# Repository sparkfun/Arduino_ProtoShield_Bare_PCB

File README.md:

SparkFun Arduino ProtoShield - Bare PCB
=======================================

<table class="table table-hover table-striped table-bordered">
  <tr align="center">
   <td></td>
   <td></td>
  </tr>
  <tr align="center">
    <td>SparkFun Arduino ProtoShield - Bare PCB [ <a href="https://www.sparkfun.com/products/13819">DEV-13819</a> ]</td>
    <td>SparkFun ProtoShield Kit [ <a href="https://www.sparkfun.com/products/13820">DEV-13820</a> ]</td>
  </tr>
</table>

The SparkFun Arduino ProtoShield is a bare PCB with no attached or included parts that lets you customize your own Arduino shield using whatever circuit you can come up with! You will even be able to test your circuit or project to make sure everything is working the way it should! The SparkFun Arduino ProtoShield is based off the Arduino R3’s footprint that allows you to easily incorporate it with favorite Arduino-based device.

Repository Contents
-------------------
* **/Firmware** - Example code used in the hookup guide.
* **/Hardware** - All Eagle design files (.brd, .sch)
* **/Production** - All Eagle design files (.brd, .sch)

Documentation
--------------
* **[Hookup Guide](https://learn.sparkfun.com/tutorials/sparkfun-arduino-protoshield-hookup-guide)** - Basic hookup guide for the SparkFun Arduino ProtoShield v40.
* _**[Quickstart Guide (RETIRED)](https://learn.sparkfun.com/tutorials/arduino-protoshield-quickstart-guide)** - Basic quickstart guide for the SparkFun Arduino ProtoShield v25._

Product Versions
----------------
* [DEV-13819](https://www.sparkfun.com/products/13819) - Bare pcb.
* [DEV-13820](https://www.sparkfun.com/products/13820) - Protoshield Kit. Bare pcb, plus stackable headers, indicator LEDs, push buttons, and resistors.
* _[DEV-11665 (RETIRED)](https://www.sparkfun.com/products/11665) - Bare pcb._
* _[DEV-07914 (RETIRED)](https://www.sparkfun.com/products/7914) - Protoshield Kit. Bare pcb plus stackable headers, indicator LEDs, push buttons and resistors._

Version History
---------------
* [V_4.0F2.0](https://github.com/sparkfun/Arduino_ProtoShield_Bare_PCB/releases/tag/V_4.0F2.0) - Revision v4.0 with updated example code.
* [V_2.5F1.0](https://github.com/sparkfun/Arduino_ProtoShield_Bare_PCB/releases/tag/V_2.5F1.0) - Initial release with example code from quickstart guide 
* [V_2.5](https://github.com/sparkfun/Arduino_ProtoShield_Bare_PCB/releases/tag/V_2.5) - Initial release

License Information
-------------------

This product is _**open source**_! 

Please review the LICENSE.md file for license information. 

If you have any questions or concerns on licensing, please contact techsupport@sparkfun.com.

Distributed as-is; no warranty is given.

- Your friends at SparkFun.

_<COLLABORATION CREDIT>_

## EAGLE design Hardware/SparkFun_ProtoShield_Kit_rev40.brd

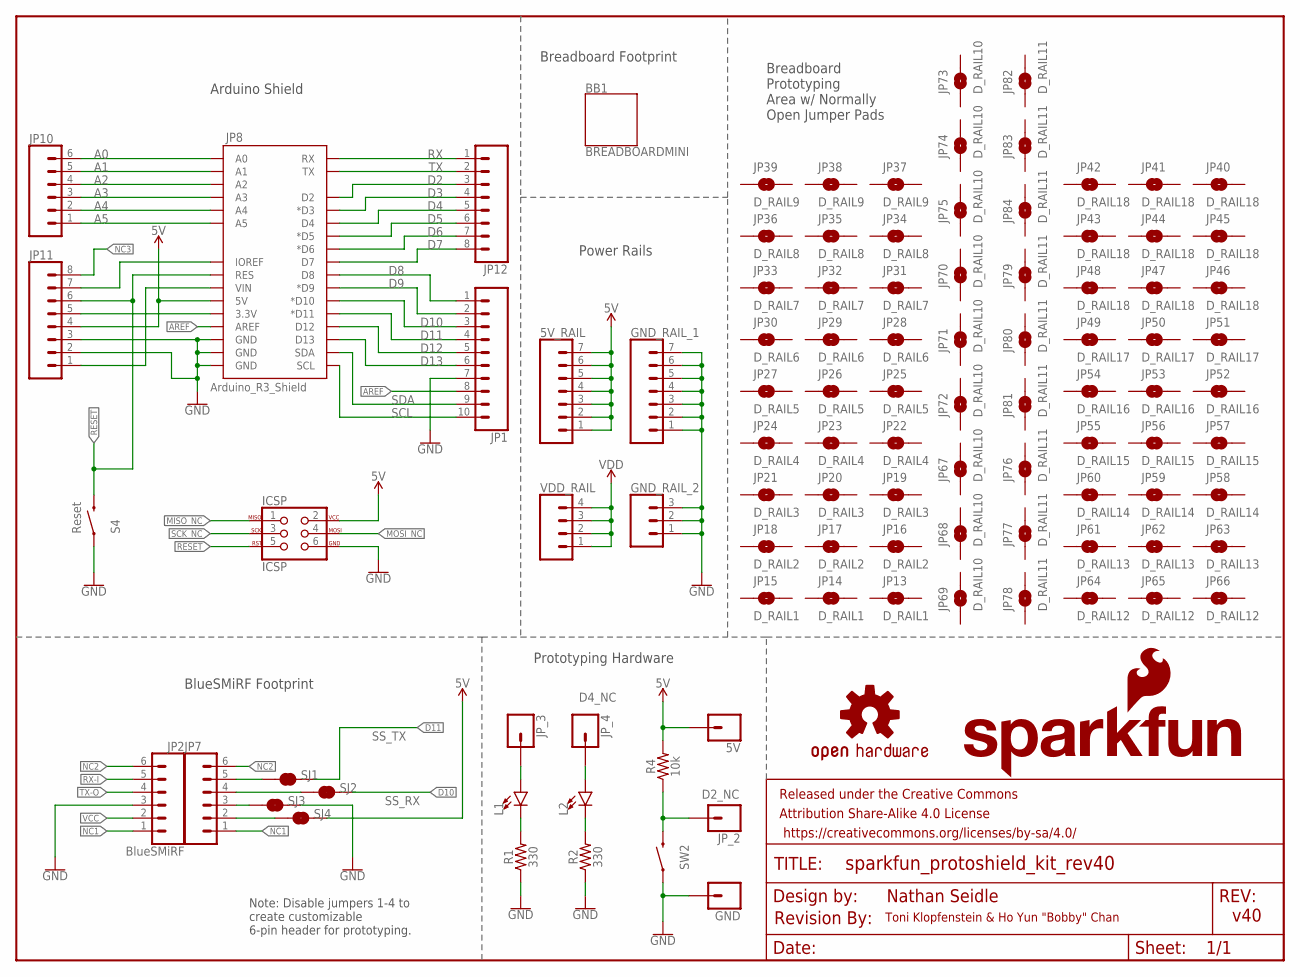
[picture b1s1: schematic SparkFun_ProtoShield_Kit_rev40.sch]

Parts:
5V: CONN_01; 1X01
5V_RAIL: CONN_07NO_SILK; 1X07_NO_SILK
BB1: BREADBOARDMINI; BREADBOARD-MINI
FRAME1: FRAME-LETTER; CREATIVE_COMMONS
GND: CONN_01; 1X01
GND_RAIL_1: CONN_07NO_SILK; 1X07_NO_SILK
GND_RAIL_2: CONN_031X03_NO_SILK; 1X03_NO_SILK
ICSP: ICSP; 2X3
JP1: CONN_10"; 1X10
JP2: BlueSMiRF; 1X06
JP7, JP10: CONN_06SILK_FEMALE_PTH; 1X06
JP8: ARDUINO_R3_SHIELDR3_PROTO_SHIELD; UNO_R3_PROTO_SHIELD
JP11, JP12: CONN_08"; 1X08
JP13, JP14, JP15: D_RAIL1; SMT-JUMPER_2_NO_NO-SILK
JP16, JP17, JP18: D_RAIL2; SMT-JUMPER_2_NO_NO-SILK
JP19, JP20, JP21: D_RAIL3; SMT-JUMPER_2_NO_NO-SILK
JP22, JP23, JP24: D_RAIL4; SMT-JUMPER_2_NO_NO-SILK
JP25, JP26, JP27: D_RAIL5; SMT-JUMPER_2_NO_NO-SILK
JP28, JP29, JP30: D_RAIL6; SMT-JUMPER_2_NO_NO-SILK
JP31, JP32, JP33: D_RAIL7; SMT-JUMPER_2_NO_NO-SILK
JP34, JP35, JP36: D_RAIL8; SMT-JUMPER_2_NO_NO-SILK
JP37, JP38, JP39: D_RAIL9; SMT-JUMPER_2_NO_NO-SILK
JP40, JP41, JP42, JP43, JP44, JP45, JP46, JP47, JP48: D_RAIL18; SMT-JUMPER_2_NO_NO-SILK
JP49, JP50, JP51: D_RAIL17; SMT-JUMPER_2_NO_NO-SILK
JP52, JP53, JP54: D_RAIL16; SMT-JUMPER_2_NO_NO-SILK
JP55, JP56, JP57: D_RAIL15; SMT-JUMPER_2_NO_NO-SILK
JP58, JP59, JP60: D_RAIL14; SMT-JUMPER_2_NO_NO-SILK
JP61, JP62, JP63: D_RAIL13; SMT-JUMPER_2_NO_NO-SILK
JP64, JP65, JP66: D_RAIL12; SMT-JUMPER_2_NO_NO-SILK
JP67, JP68, JP69, JP70, JP71, JP72, JP73, JP74, JP75: D_RAIL10; SMT-JUMPER_2_NO_NO-SILK
JP76, JP77, JP78, JP79, JP80, JP81, JP82, JP83, JP84: D_RAIL11; SMT-JUMPER_2_NO_NO-SILK
JP_2, JP_3, JP_4: CONN_01; 1X01
L1, L2: LED3MM; LED_3MM
LOGO1: OSHW-LOGOS; OSHW-LOGO-S
R1, R2: 330; AXIAL-0.3
R4: 10k; AXIAL-0.3
S4: MOMENTARY-SWITCH-SPST-PTH-6.0MM; TACTILE_SWITCH_PTH_6.0MM
SJ1, SJ2, SJ3, SJ4: JUMPER-SMT_2_NC_TRACE_SILK; SMT-JUMPER_2_NC_TRACE_SILK
SW2: MOMENTARY-SWITCH-SPST-PTH-6.0MM; TACTILE_SWITCH_PTH_6.0MM
U$1: SFE_LOGO_NAME_FLAME.1_INCH; SFE_LOGO_NAME_FLAME_.1
U$2: REVISION
VDD_RAIL: CONN_041X04_NO_SILK; 1X04_NO_SILK

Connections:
3.3: JP8.3.3V, JP11.5
5V: 5V.1, 5V_RAIL.1, 5V_RAIL.2, 5V_RAIL.3, 5V_RAIL.4, 5V_RAIL.5, 5V_RAIL.6, 5V_RAIL.7, ICSP.2, JP8.5V, JP11.4, R4.P$2 (2), SJ4.2
A1: JP8.A1, JP10.5
A2: JP8.A2, JP10.4
A5: JP8.A5, JP10.1
AREF: JP1.8, JP8.AREF
D2: JP8.D2, JP12.3
D2_NC: JP_2.1, R4.P$1 (1), SW2.3 (2)
D3: JP8.D3 (*D3), JP12.4
D4: JP8.D4, JP12.5
D5: JP8.D5 (*D5), JP12.6
D6: JP8.D6 (*D6), JP12.7
D7: JP8.D7, JP12.8
D8: JP1.1, JP8.D8
D9: JP1.2, JP8.D9 (*D9)
D10: JP1.3, JP8.D10 (*D10), SJ2.2
D11: JP1.4, JP8.D11 (*D11), SJ1.2
D12: JP1.5, JP8.D12
D13: JP1.6, JP8.D13
GND: GND.1, GND_RAIL_1.1, GND_RAIL_1.2, GND_RAIL_1.3, GND_RAIL_1.4, GND_RAIL_1.5, GND_RAIL_1.6, GND_RAIL_1.7, GND_RAIL_2.1, GND_RAIL_2.2, GND_RAIL_2.3, ICSP.6, JP1.7, JP2.3, JP7.3, JP8.GND@0 (GND), JP8.GND@1 (GND), JP8.GND@2 (GND), JP11.2, JP11.3, R1.P$1 (1), R2.P$1 (1), S4.1, SJ3.1, SJ3.2, SW2.1
JP3: JP_3.1, L1.A
JP4: JP_4.1, L2.A
MISO_NC: ICSP.1
MOSI_NC: ICSP.4
unnamed: JP8.IOREF, JP11.7
unnamed: JP8.A0, JP10.6
unnamed: JP8.A4, JP10.2
unnamed: JP8.A3, JP10.3
unnamed: L1.K (C), R1.P$2 (2)
unnamed: L2.K (C), R2.P$2 (2)
NC1: JP2.1, JP7.1
NC2: JP2.6, JP7.6
NC3: JP11.8
RESET: ICSP.5, JP8.RES, JP11.6, S4.3 (2)
RX: JP8.RX, JP12.1
RX-I: JP2.5, JP7.5, SJ1.1
SCK_NC: ICSP.3
SCL: JP1.10, JP8.SCL
SDA: JP1.9, JP8.SDA
TX: JP8.TX, JP12.2
TX-O: JP2.4, JP7.4, SJ2.1
VCC: JP2.2, JP7.2, SJ4.1
VDD: VDD_RAIL.1, VDD_RAIL.2, VDD_RAIL.3, VDD_RAIL.4
VIN: JP8.VIN, JP11.1

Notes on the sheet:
Nathan Seidle
v40
Toni Klopfenstein & Ho Yun "Bobby" Chan
Arduino Shield
Power Rails
Prototyping Hardware
Breadboard Footprint
BlueSMiRF Footprint
Note: Disable jumpers 1-4 to create customizable 6-pin header for prototyping.
Arduino_R3_Shield
Reset
SS_TX
SS_RX
Breadboard Prototyping Area w/ Normally Open Jumper Pads
D4_NC

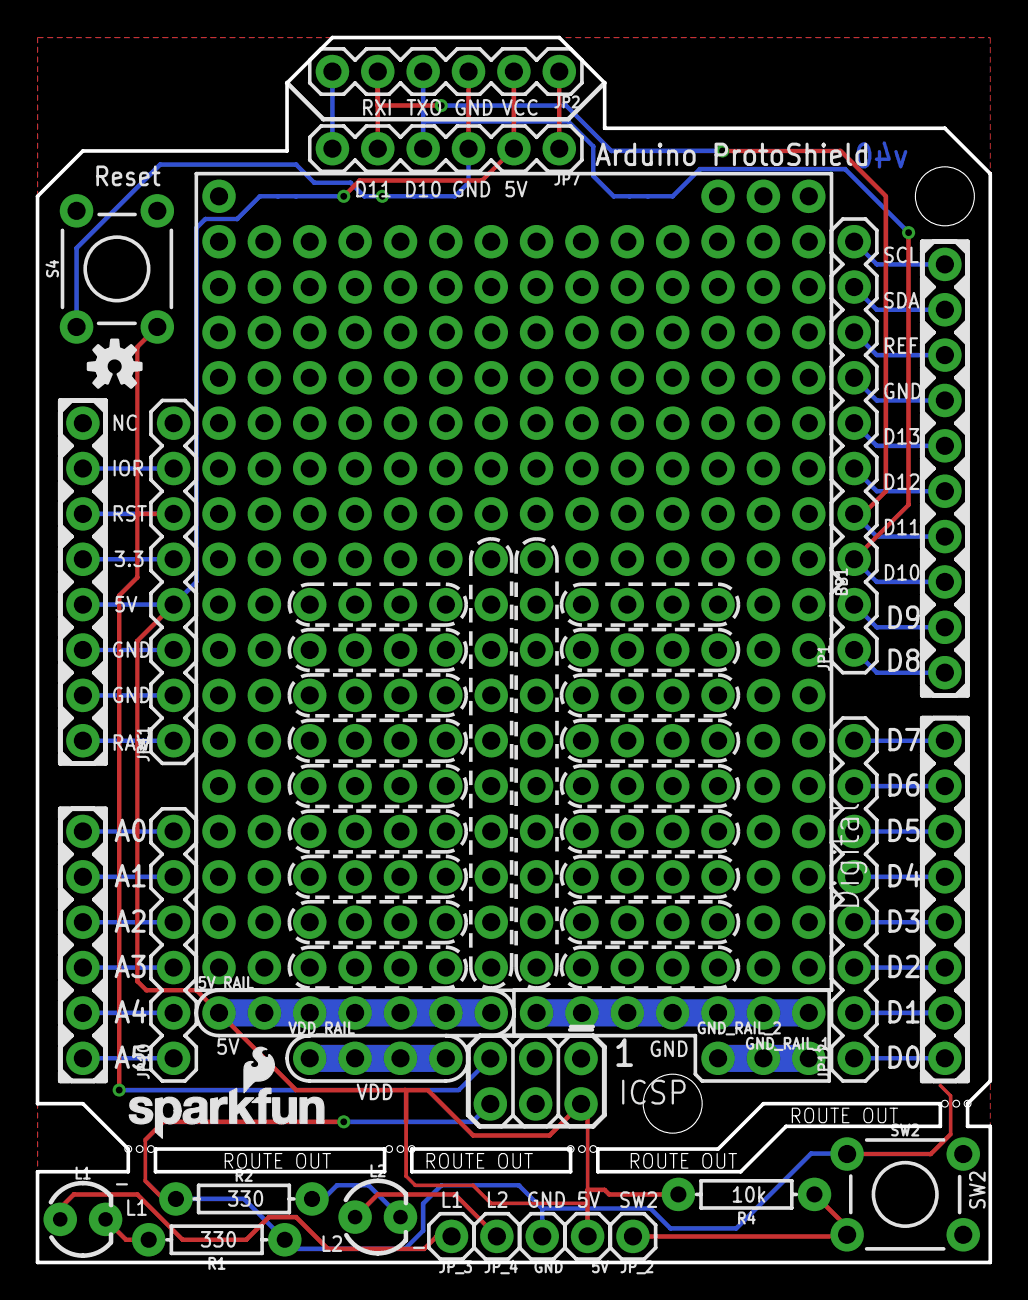
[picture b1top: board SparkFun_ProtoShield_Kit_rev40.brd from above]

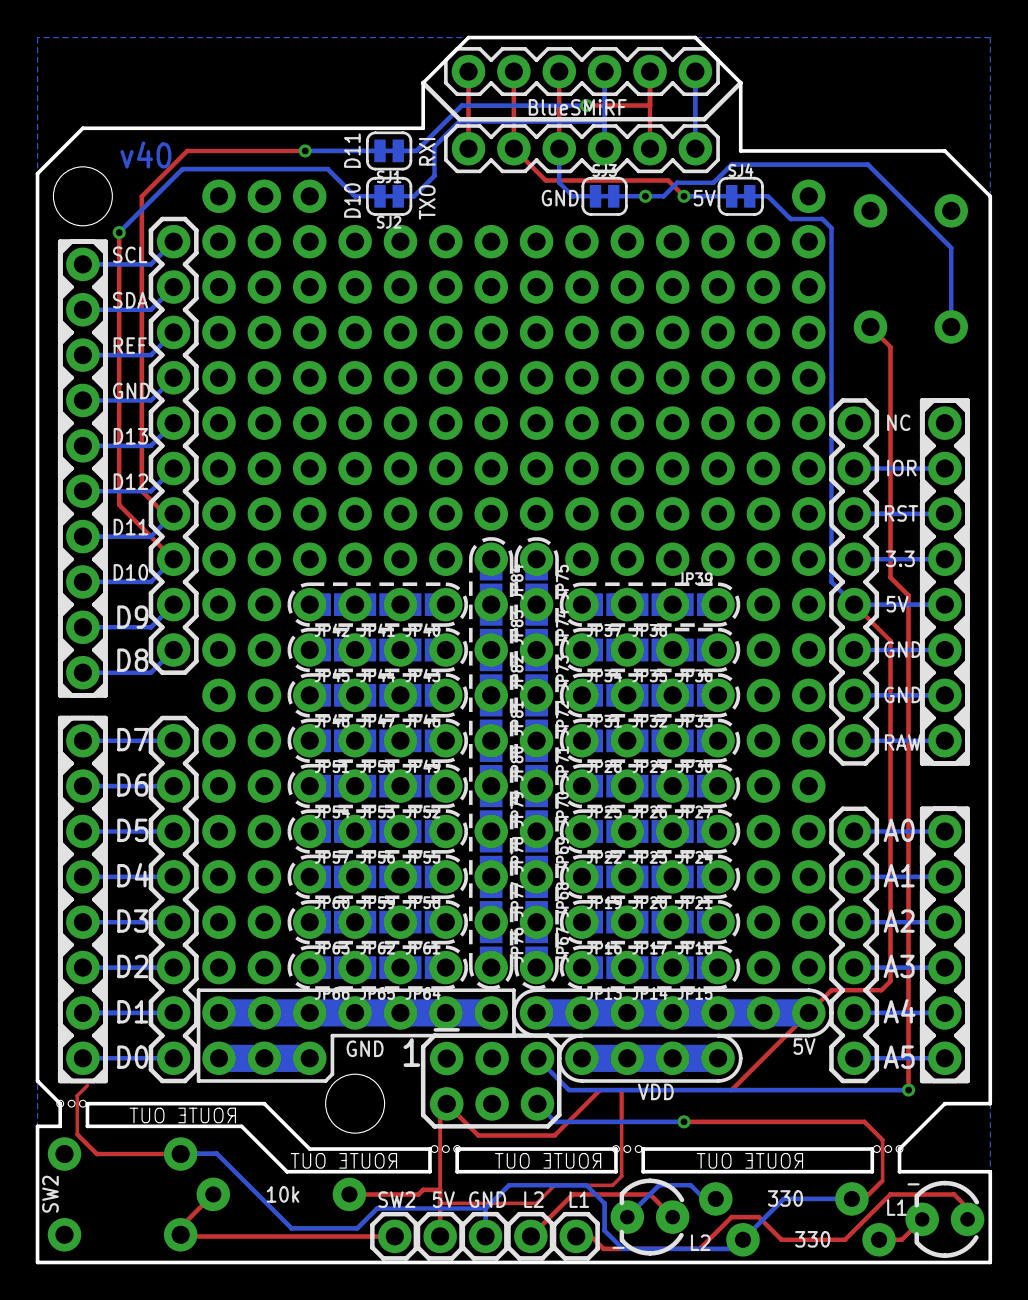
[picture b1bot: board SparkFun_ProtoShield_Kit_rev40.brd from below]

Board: 2 copper layers, 53.3 x 68.6 mm, 105 parts (76 on the bottom side), 40 nets.

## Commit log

2015-05-04 Adding hardware files, updating readme
2015-09-01 Adidng license file
2015-09-02 WIP - basic hardware layout changes
2015-09-03 Ready for engineering review
2015-09-15 Fixing part names, adding additional connector from engineering review
2015-09-29 Updates from engineering review
2015-12-02 WIP-bumping annular rings
2015-12-03 Updates from checklist
2016-02-08 Fixing QC checks on silk labels, ROUTE OUT note
2017-10-31 Add files via upload
    -updated labels and silkscreen
    -changed names to vectors
    -flipped the BlueSMiRF header's orientation so that the bluetooth faces out away from the board
    -modified traces for the BlueSMiRF
2017-11-01 Revert "Merge pull request #7 from bboyho/Revision"
2017-11-02 Update files
    **Board**
    * Align the 5V/GND silk screen.
    * Replace the SparkFun logo with a SparkFun logo w/flame, in the SparkFun Aesthetics library.
    * Add the silk for the Arduino PTH headers on the bottom side as well.
    * Fix placement and size of the BlueSMiRF text on the underside of the shield.
    * Add silkscreen for the UART pins for BlueSMiRF.
2017-11-02 Update file name to reflect revision
2017-11-02 Update File Name
2017-11-06 Add files via upload
    **Board**
    * Change wire boundary to bRestrict layer to prevent ground pour from creating a thermal around GND jumper pads.
    **Schematic**
    * Move OSHW logo next to SparkFun logo
    * Move schematic components around to make use of the empty space
2017-11-07 Add files via upload
    Add more tRestrict and bRestrict boundaries so that ground pours do not connect to GND pin after jumper.
2017-11-07 Delete SparkFun_ProtoShield_Kit_rev31.b#1
    manually delete backup file
2018-01-24 Update_Proto2
    -Shifted the mini-breadboard footprint
    -Moved Vcc and GND rails to bottom for access
    -Added VDD as an option
    -Added Disconnected Breadboard rails based on Jim’s Design (GPS Shield), best of both worlds
    -Add 2x more through hole pins for prototyping area
    -Shifted Prototyping Hardware Around
2018-02-05 Proto 2 QC Update
    -Adjust normally open (NO) jumper pad rails so the silkscreen is not over the vias to prevent errors.
    -Adjust the "+" 5V trace intersection for the prototyping hardware.
2018-02-06 Airwires
    -Fix airwires on analog pins, 5V rail, and VDD rail.
    -Fix tiny floating net wire in schematic.
2018-03-23 Create BT__Serial_Passthrough.ino
    test code bluetooth firmware on software serial pins
2018-04-14 Update Dimensions
    - Update dimensions (layer 47) in Eagle file for x and y instead of having it for the chamfered measurements.
    - Add dimensions between mounting hole's center and the edge of board
2018-04-16 Update to v40
    -Update SCH version number
    -Update BRD version number in copper
    -Update file names
2018-04-18 created v40 board
2018-05-17 Example Code
2018-05-17 Remove Old Example Code
    Since the old example code is saved in the old tutorial and tagged in the GitHub repo, I am removing it from the current master.

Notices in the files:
parts and their libraries:
SparkFun-Aesthetics: Licensing: Creative Commons ShareAlike 4.0 International - https://creativecommons.org/licenses/by-sa/4.0
SparkFun-Aesthetics: Released under the Creative Commons Attribution Share-Alike 4.0 License
SparkFun-Aesthetics: https://creativecommons.org/licenses/by-sa/4.0
